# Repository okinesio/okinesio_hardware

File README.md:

# okinesio | Hardware files

This repository contains resources for the okinesio boards.

Head over to [okinesio.org/hardware](http://okinesio.org/hardware) for an overview.

License Information
-------------------
The hardware designs are released under [CC-SA v3 license](http://creativecommons.org/licenses/by-sa/3.0).

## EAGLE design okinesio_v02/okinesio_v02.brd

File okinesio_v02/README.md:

# okinesio v0.2

Version 0.2 comes with slight changes in layout:
Smaller footprints for some components and the resonator is replaced by a more precise quartz crystal.

```
Size:    approx. 30.8 x 20 mm

Operating Voltage:     3.3V
Input Voltage:         3-5V
Clock Speed:           8MHz

Microcontroller: ATmega32U4
Flash:                32 KB
SRAM:                2.5 KB
EEPROM:                1 KB
```

Eagle files and schematics are modified and extended versions of the original files from [LilyPad Arduino USB](https://github.com/sparkfun/LilyPad_Arduino_USB).

License Information
-------------------
The hardware design is released under [CC-SA v3 license](http://creativecommons.org/licenses/by-sa/3.0).

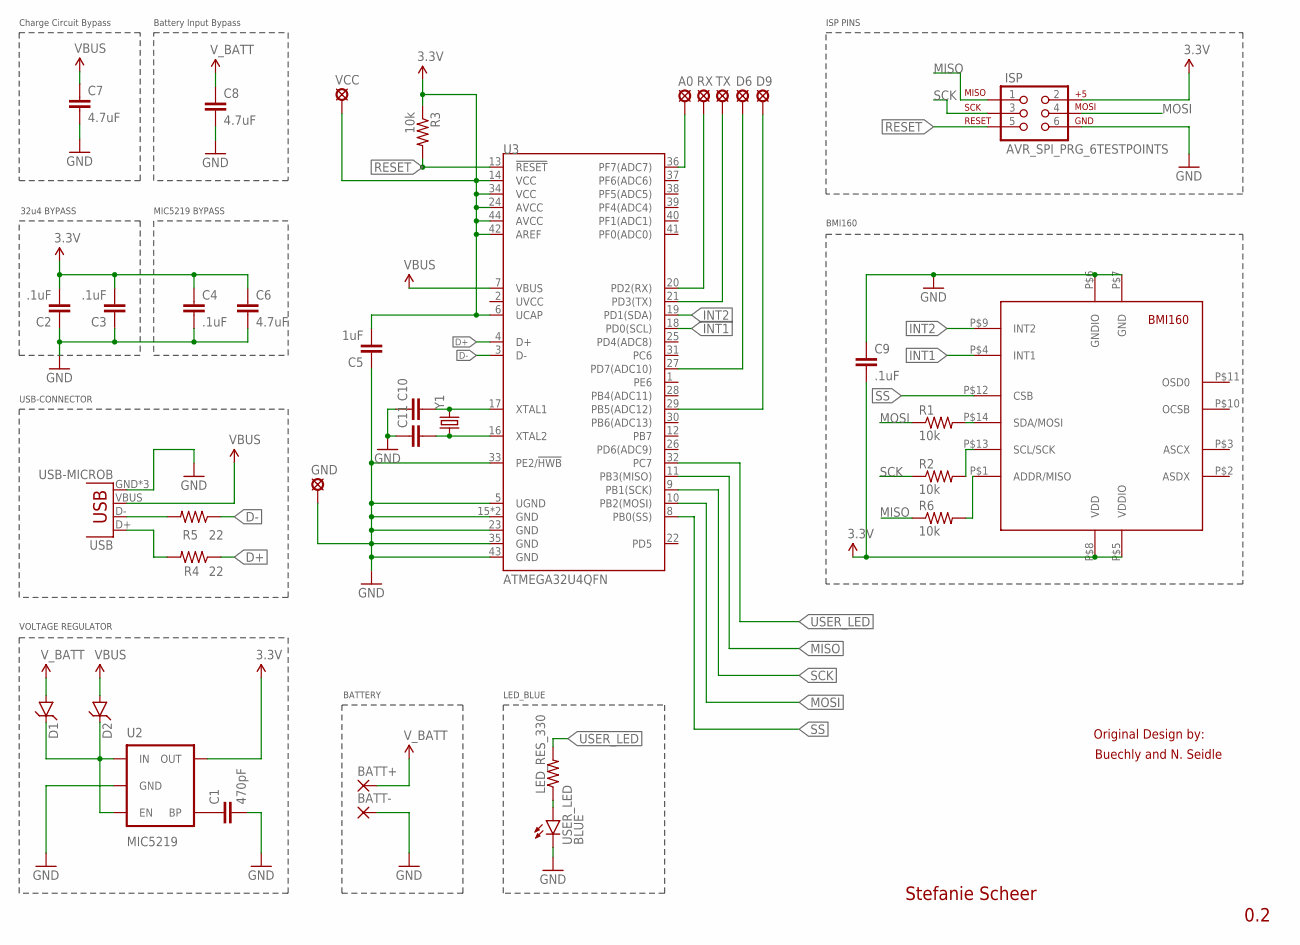
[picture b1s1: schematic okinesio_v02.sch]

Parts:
A0: LSP10
BATT+: SMD2; SMD1,27-2,54
BATT-: SMD2; SMD1,27-2,54
C1: 470pF; 0603-CAP
C2, C3, C4, C9: .1uF; 0603-CAP
C5: 1uF; 0603-CAP
C6: 4.7uF; 0603-CAP
C7, C8: 4.7uF; 0805
C10, C11: CAP0603-CAP; 0603-CAP
D1, D2: DIODESOD123; SOD-123
D6, D9: LSP10
GND: LSP10
ISP: AVR_SPI_PRG_6TESTPOINTS; 2X3_TEST_POINTS
LED_RES_330: RESISTOR0603; 0603-RES
R1, R2, R3, R6: 10k; 0603-RES
R4, R5: 22; 0603-RES
RX: LSP10
TX: LSP10
U2: MIC5219; SOT23-5
U3: ATMEGA32U4QFN; QFN-44
U$3: BMI160LGA14; LGA14-BMI160
USB: USB-MICROB
USER_LED: BLUE; LED-0603
VCC: LSP10
Y1: CRYSTALTXC-7A; CRYSTAL-TXC-7A

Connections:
3.3V: C2.2, C3.2, C4.1, C5.2, C6.1, C9.2, ISP.2, R3.1, U2.5 (OUT), U3.6 (UCAP), U3.14 (VCC), U3.24 (AVCC), U3.34 (VCC), U3.42 (AREF), U3.44 (AVCC), U$3.P$5 (VDDIO), U$3.P$8 (VDD), VCC.MP
5V: C7.1, D2.A, U3.7 (VBUS), USB.VBUS
D+: R4.1, U3.4 (D+)
D-: R5.1, U3.3 (D-)
GND: BATT-.1, C1.2, C2.1, C3.1, C4.2, C5.1, C6.2, C7.2, C8.2, C9.1, C10.1, C11.1, GND.MP, ISP.6, U2.2 (GND), U3.5 (UGND), U3.15 (GND), U3.23 (GND), U3.33 (PE2/!HWB), U3.35 (GND), U3.43 (GND), U3.EPAD (GND), U$3.P$6 (GNDIO), U$3.P$7 (GND), USB.GND, USB.MT1 (GND), USB.MT2 (GND), USER_LED.C
INT1: U3.18 (PD0(SCL)), U$3.P$4 (INT1)
INT2: U3.19 (PD1(SDA)), U$3.P$9 (INT2)
MISO: ISP.1, R6.1, U3.11 (PB3(MISO))
MOSI: ISP.4, R1.1, U3.10 (PB2(MOSI))
unnamed: D1.C, D2.C, U2.1 (IN), U2.3 (EN)
unnamed: D6.MP, U3.27 (PD7(ADC10))
unnamed: TX.MP, U3.21 (PD3(TX))
unnamed: A0.MP, U3.36 (PF7(ADC7))
unnamed: C10.2, U3.17 (XTAL1), Y1.P$2 (2)
unnamed: D9.MP, U3.29 (PB5(ADC12))
unnamed: LED_RES_330.1, USER_LED.A
unnamed: C1.1, U2.4 (BP)
unnamed: RX.MP, U3.20 (PD2(RX))
unnamed: R1.2, U$3.P$14 (SDA/MOSI)
unnamed: R5.2, USB.D-
unnamed: R4.2, USB.D+
unnamed: R2.2, U$3.P$13 (SCL/SCK)
unnamed: R6.2, U$3.P$1 (ADDR/MISO)
unnamed: C11.2, U3.16 (XTAL2), Y1.P$1 (1)
RESET: ISP.5, R3.2, U3.13 (!RESET)
SCK: ISP.3, R2.1, U3.9 (PB1(SCK))
SS: U3.8 (PB0(SS)), U$3.P$12 (CSB)
USER_LED: LED_RES_330.2, U3.32 (PC7)
V_BATT: BATT+.1, C8.1, D1.A

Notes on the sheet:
32u4 BYPASS
MIC5219 BYPASS
Charge Circuit Bypass
Battery Input Bypass
Original Design by:
Stefanie Scheer
0.2
Buechly and N. Seidle
USB-CONNECTOR
VOLTAGE REGULATOR
BATTERY
LED_BLUE
ISP PINS
BMI160

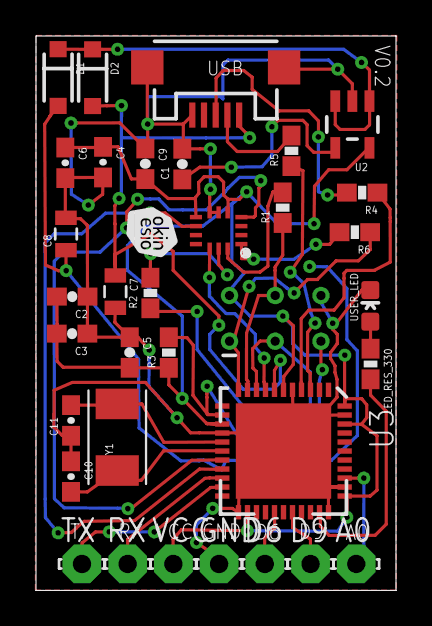
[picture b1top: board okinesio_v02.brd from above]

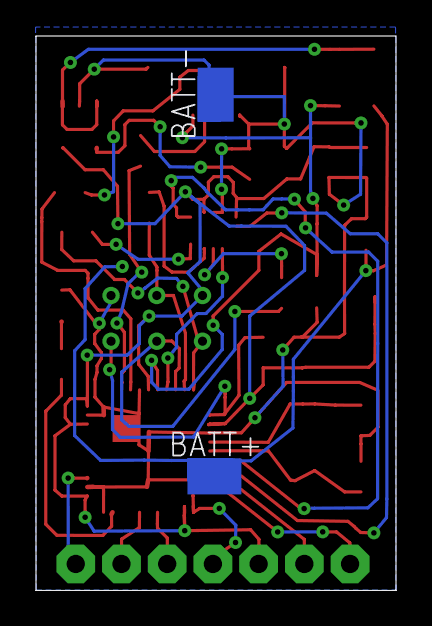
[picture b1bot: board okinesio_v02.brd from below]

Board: 2 copper layers, 20.0 x 30.8 mm, 36 parts (2 on the bottom side), 29 nets.

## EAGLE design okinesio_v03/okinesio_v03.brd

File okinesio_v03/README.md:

# okinesio v0.3

The latest version with completely new layout. Featuring an on-board lipo charger and lipo connector which replaces the coin cell.
With the BMM150 (magnetometer) the board is adding up to 9-DOF and there is a microSD card reader on the backside.

```
Size:    approx. 30 x 20 mm

Operating Voltage:     3.3V
Input Voltage:         3-5V
Clock Speed:           8MHz

Microcontroller: ATmega32U4
Flash:                32 KB
SRAM:                2.5 KB
EEPROM:                1 KB
```

Eagle files and schematics are modified and extended versions of the original files from [LilyPad Arduino USB](https://github.com/sparkfun/LilyPad_Arduino_USB).

License Information
-------------------
The hardware design is released under [CC-SA v3 license](http://creativecommons.org/licenses/by-sa/3.0).

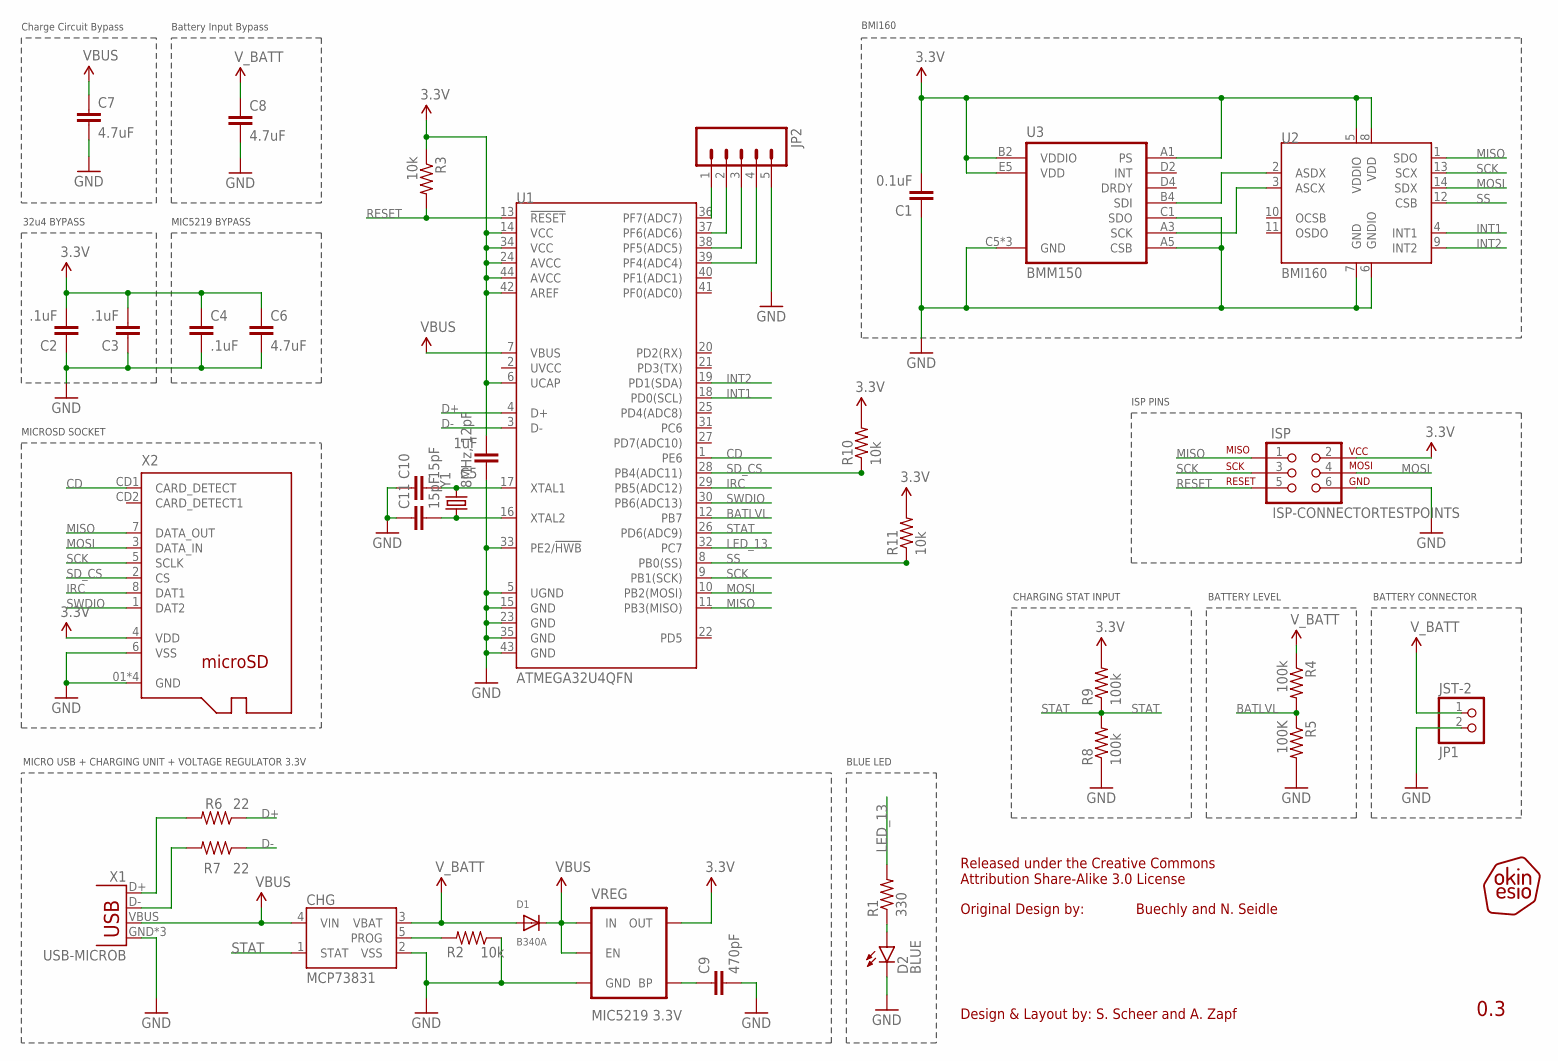
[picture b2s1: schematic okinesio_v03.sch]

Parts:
C1: 0.1uF; 0603-CAP
C2, C3, C4: .1uF; 0603-CAP
C5: 1uF; 0603-CAP
C6: 4.7uF; 0603-CAP
C7, C8: 4.7uF; 0805
C9: 470pF; 0603-CAP
C10, C11: 15pF; 0603-CAP
CHG: MCP73831; SOT23-5
D1: B340A; SOD-123
D2: BLUE; LED-0603
ISP: ISP-CONNECTORTESTPOINTS; 2X3_TEST_POINTS
JP1: JST-2; JST-PH-2-THM-RA
JP2: M05PTH; 1X05
R1: 330; 0603-RES
R2, R3, R10, R11: 10k; 0603-RES
R4, R8, R9: 100k; 0603-RES
R5: 100K; 0603-RES
R6, R7: 22; 0603-RES
U1: ATMEGA32U4QFN; QFN-44
U2: BMI160LGA14; LGA14-BMI160
U3: BMM150; WLCSP12-1.56X1.56
U$4: OKINESIO-LOGO-2.85X2.81MM; LOGO-STANDARD
VREG: MIC5219 3.3V; SOT23-5
X1: USB-MICROB
X2: MICROSD-SOCKET
Y1: 8MHz, 12pF; CRYSTAL-TXC-7A

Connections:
3.3V: C1.2, C2.2, C3.2, C4.1, C5.2, C6.1, ISP.2, R3.1, R9.2, R10.2, R11.2, U1.6 (UCAP), U1.14 (VCC), U1.24 (AVCC), U1.34 (VCC), U1.42 (AREF), U1.44 (AVCC), U2.5 (VDDIO), U2.8 (VDD), U3.A1 (PS), U3.B2 (VDDIO), U3.E5 (VDD), VREG.5 (OUT), X2.4 (VDD)
5V: C7.1, CHG.4 (VIN), D1.C, U1.7 (VBUS), VREG.1 (IN), VREG.3 (EN), X1.VBUS
BATLVL: R4.2, R5.1, U1.12 (PB7)
CD: U1.1 (PE6), X2.CD1 (CARD_DETECT)
D+: R6.1, U1.4 (D+)
D-: R7.1, U1.3 (D-)
GND: C1.1, C2.1, C3.1, C4.2, C5.1, C6.2, C7.2, C8.2, C9.2, C10.1, C11.1, CHG.2 (VSS), D2.C, ISP.6, JP1.2 (1), JP2.5, R2.1, R5.2, R8.1, U1.5 (UGND), U1.15 (GND), U1.23 (GND), U1.33 (PE2/!HWB), U1.35 (GND), U1.43 (GND), U2.6 (GNDIO), U2.7 (GND), U3.A5 (CSB), U3.C1 (SDO), U3.C5 (GND), U3.E1 (GND), U3.E3 (GND), VREG.2 (GND), X1.GND, X1.MT1 (GND), X1.MT2 (GND), X2.01 (GND), X2.02 (GND), X2.03 (GND), X2.04 (GND), X2.6 (VSS)
INT1: U1.18 (PD0(SCL)), U2.4 (INT1)
INT2: U1.19 (PD1(SDA)), U2.9 (INT2)
IRC: U1.29 (PB5(ADC12)), X2.8 (DAT1)
LED_13: R1.2, U1.32 (PC7)
MISO: ISP.1, U1.11 (PB3(MISO)), U2.1 (SDO), X2.7 (DATA_OUT)
MOSI: ISP.4, U1.10 (PB2(MOSI)), U2.14 (SDX), X2.3 (DATA_IN)
unnamed: U2.2 (ASDX), U3.B4 (SDI)
unnamed: JP2.1, U1.36 (PF7(ADC7))
unnamed: JP2.2, U1.37 (PF6(ADC6))
unnamed: JP2.3, U1.38 (PF5(ADC5))
unnamed: C10.2, U1.17 (XTAL1), Y1.P$2 (2)
unnamed: JP2.4, U1.39 (PF4(ADC4))
unnamed: D2.A, R1.1
unnamed: U2.3 (ASCX), U3.A3 (SCK)
unnamed: CHG.5 (PROG), R2.2
unnamed: C9.1, VREG.4 (BP)
unnamed: C11.2, U1.16 (XTAL2), Y1.P$1 (1)
unnamed: R7.2, X1.D-
unnamed: R6.2, X1.D+
RESET: ISP.5, R3.2, U1.13 (!RESET)
SCK: ISP.3, U1.9 (PB1(SCK)), U2.13 (SCX), X2.5 (SCLK)
SD_CS: R10.1, U1.28 (PB4(ADC11)), X2.2 (CS)
SS: R11.1, U1.8 (PB0(SS)), U2.12 (CSB)
STAT: CHG.1 (STAT), R8.2, R9.1, U1.26 (PD6(ADC9))
SWDIO: U1.30 (PB6(ADC13)), X2.1 (DAT2)
V_BATT: C8.1, CHG.3 (VBAT), D1.A, JP1.1 (2), R4.1

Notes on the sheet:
32u4 BYPASS
MIC5219 BYPASS
Charge Circuit Bypass
Battery Input Bypass
Original Design by:
Buechly and N. Seidle
BATTERY CONNECTOR
BLUE LED
BMI160
MICRO USB + CHARGING UNIT + VOLTAGE REGULATOR 3.3V
BATTERY LEVEL
CHARGING STAT INPUT
MICROSD SOCKET
Released under the Creative Commons Attribution Share-Alike 3.0 License
0.3
Design & Layout by: S. Scheer and A. Zapf
ISP PINS

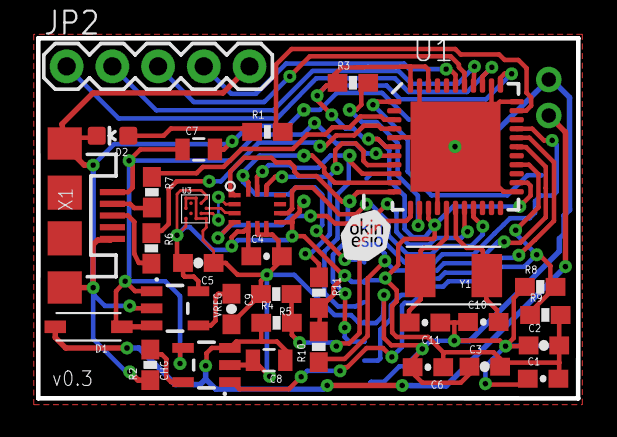
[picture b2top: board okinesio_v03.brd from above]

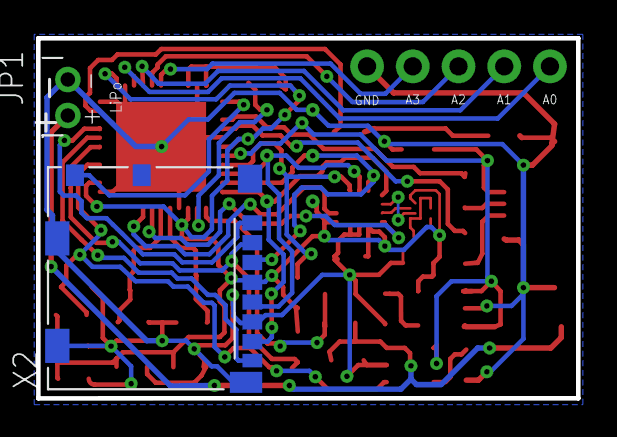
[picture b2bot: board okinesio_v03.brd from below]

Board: 2 copper layers, 30.0 x 20.0 mm, 36 parts (2 on the bottom side), 33 nets.

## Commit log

2016-05-04 Update README.md
    changed link to point to the LilyPad Github repository.
2016-05-04 added board and schematic files
2016-05-04 added schematic as PDF
2017-06-27 Added hardware files
    Added files for okinesio v0.2 and v0.3.
    Moved okinesio v0.1 into folder and changed repository name.
2018-03-27 moved package definitions in schematic on the same layer as in the board file so they are consistent again in newer versions of eagle

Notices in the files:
parts and their libraries:
SparkFun-Passives: Licensing: CC v3.0 Share-Alike You are welcome to use this library for commercial purposes.
User-Submitted: Licensing: Creative Commons ShareAlike 4.0 International - https://creativecommons.org/licenses/by-sa/4.0
